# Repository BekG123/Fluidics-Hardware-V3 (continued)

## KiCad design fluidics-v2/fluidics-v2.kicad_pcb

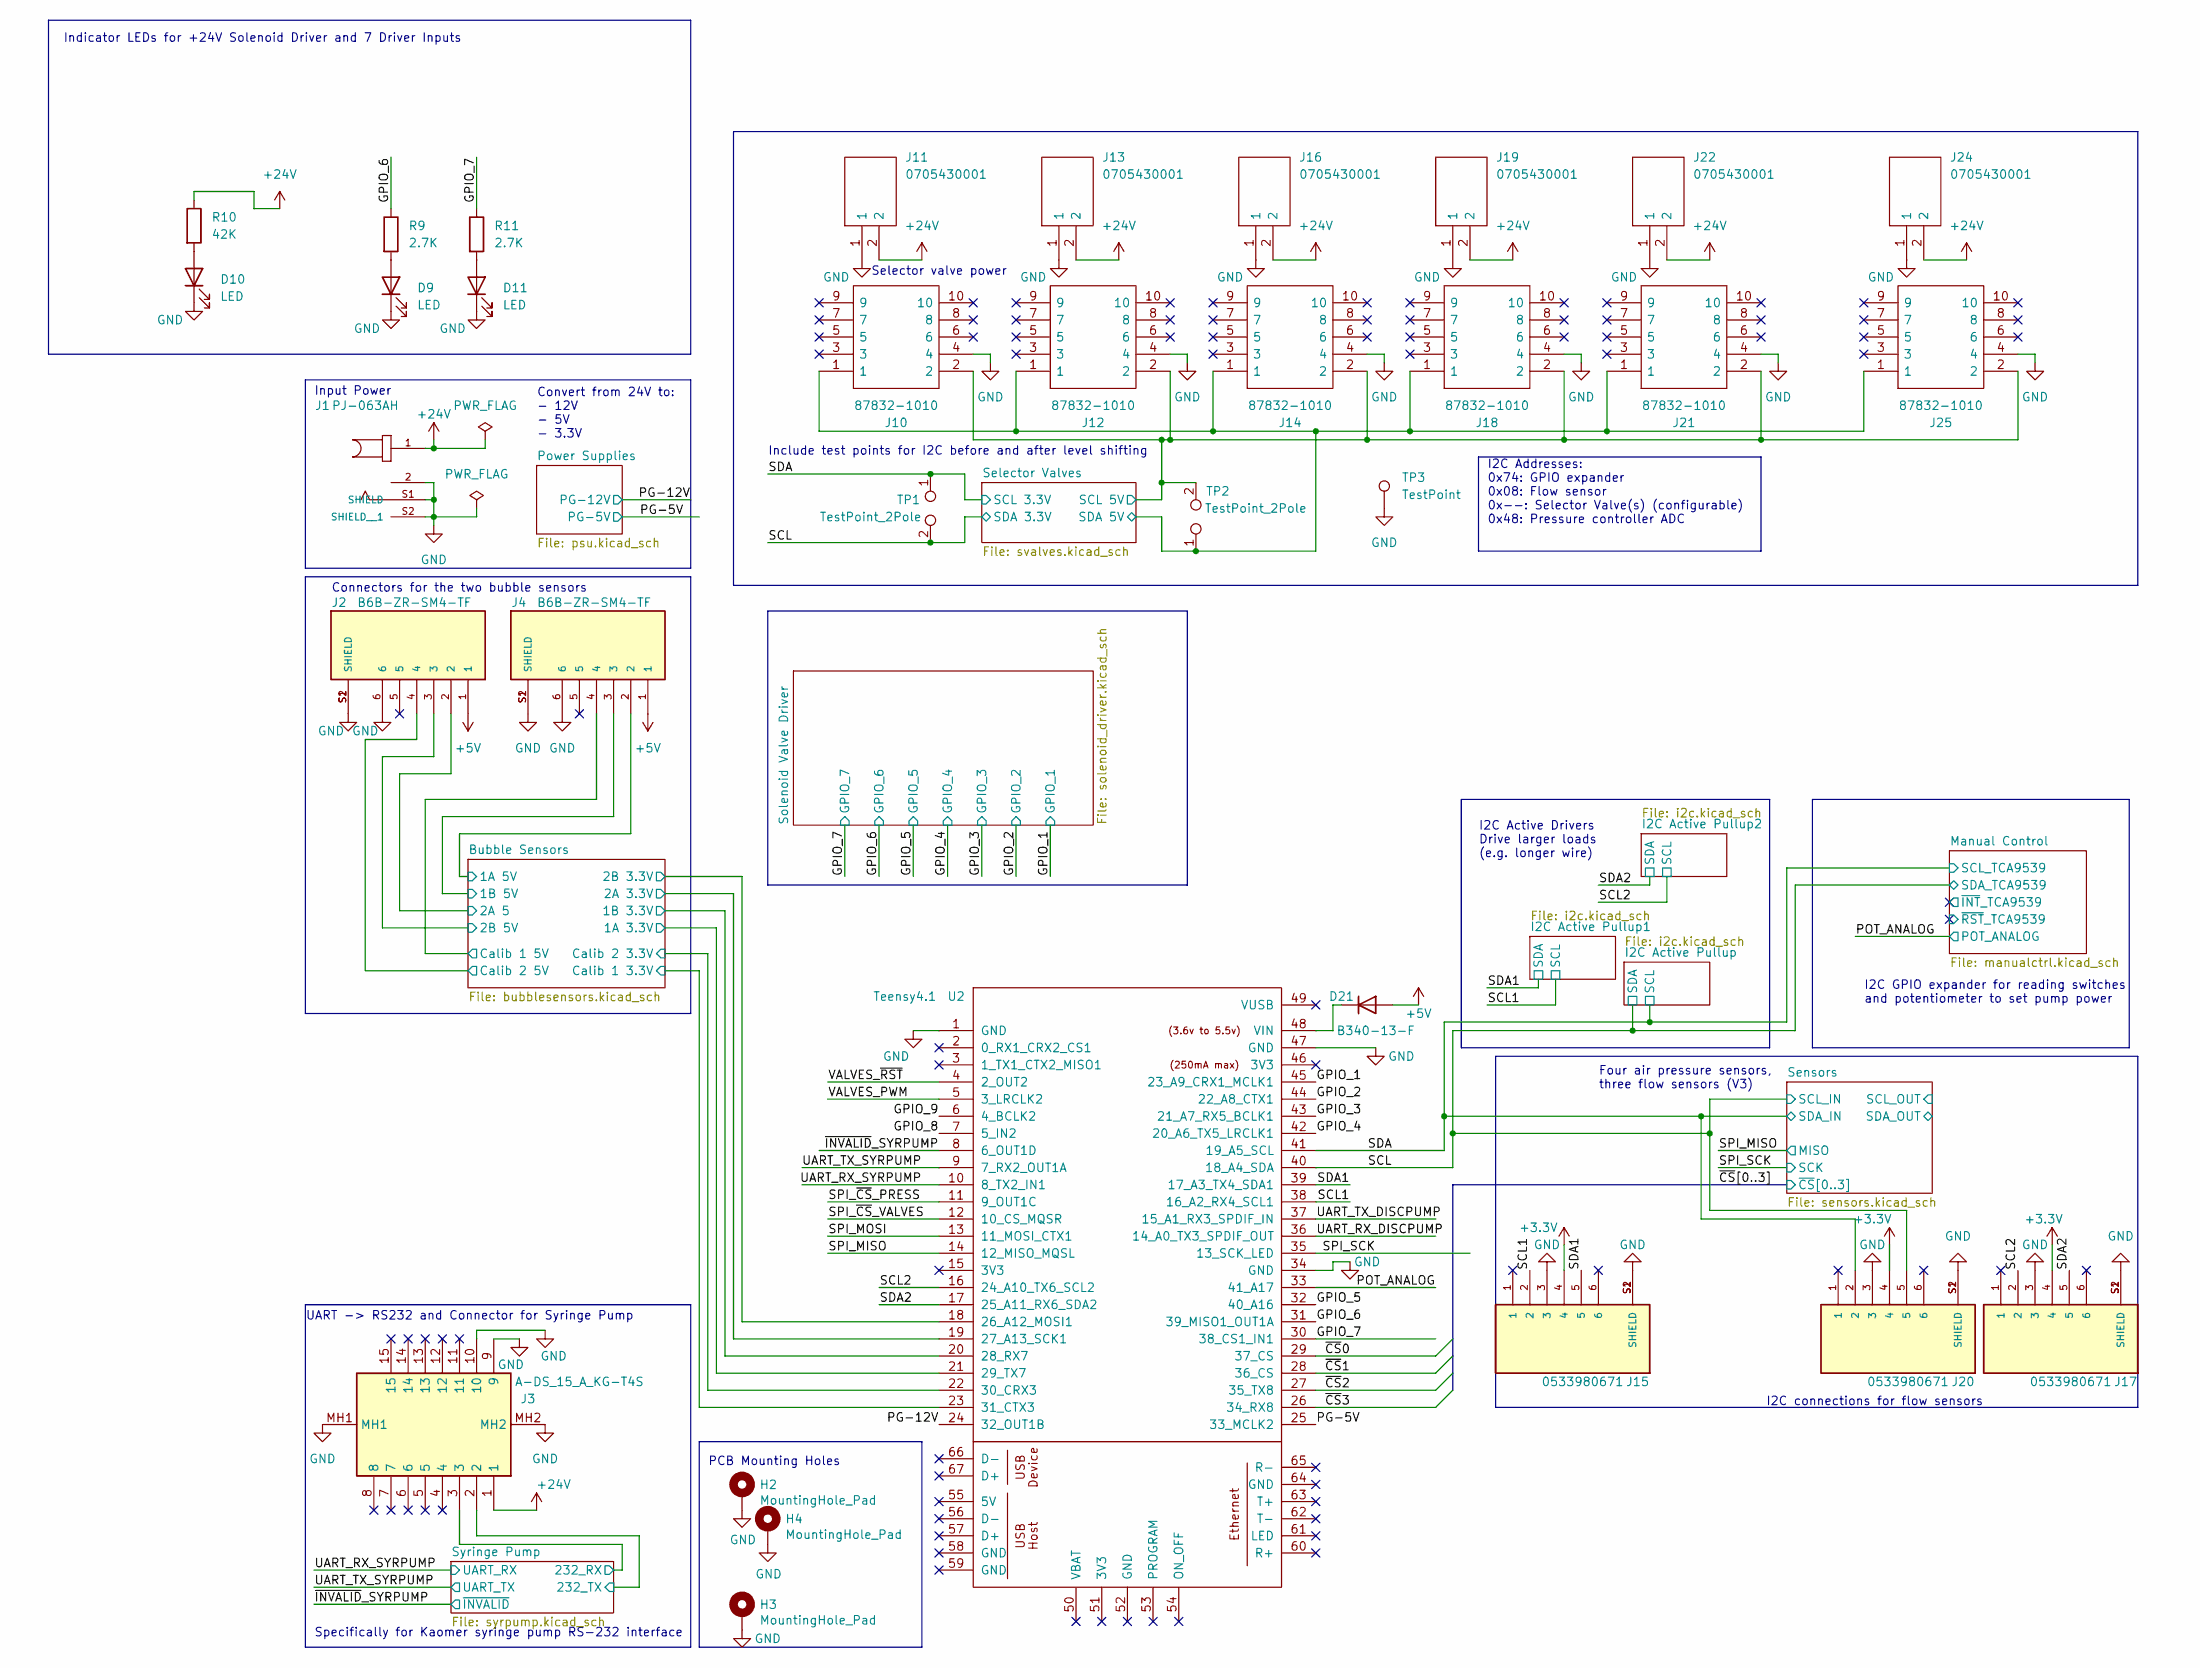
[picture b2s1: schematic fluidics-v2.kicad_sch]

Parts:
D9, D10, D11: LED; LED_0402_1005Metric
D21: B340-13-F; D_SMC
H2, H3, H4: MountingHole_Pad; MountingHole_2.2mm_M2_Pad_Via
J1: PJ-063AH; CUI_PJ-063AH; PARTREV 1.02; LCSC C2928097
J2, J4: B6B-ZR-SM4-TF; CONN_B6B-ZR-SM4-TF_JST
J3: A-DS_15_A_KG-T4S; ADS15AKGT4S; Manufacturer_Part_Number A-DS 15 A/KG-T4S; LCSC C3100941
J10, J12, J14, J18, J21, J25: 87832-1010; 878321010; Manufacturer_Part_Number 87832-1010; Mouser Part Number 538-87832-1010
J11, J13, J16, J19, J22, J24: 0705430001; SHDR2W64P0X254_1X2_737X660X1181P; Manufacturer_Part_Number 0705430001; Mouser Part Number N/A
J15, J17, J20: 0533980671; MOLEX_0533980671; PARTREV A
R9, R11: 2.7K; R_0402_1005Metric
R10: 42K; R_0603_1608Metric
TP1, TP2: TestPoint_2Pole; TestPoint_2Pads_Pitch2.54mm_Drill0.8mm
TP3: TestPoint; TestPoint_THTPad_1.5x1.5mm_Drill0.7mm
U2: Teensy4.1; Teensy 4.1

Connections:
+3.3V: J15.4, J17.4, J20.4; also elsewhere on the board
+5V: D21.2 (A), J2.1, J4.1; also elsewhere on the board
+24V: J1.1, J3.1, J11.2, J13.2, J16.2, J19.2, J22.2, J24.2, R10.1; also elsewhere on the board
/Bubble Sensors/1A 3.3V: U2.21 (29_TX7); also elsewhere on the board
/Bubble Sensors/1A 5V: J4.2; also elsewhere on the board
/Bubble Sensors/1B 3.3V: U2.20 (28_RX7); also elsewhere on the board
/Bubble Sensors/1B 5V: J4.3; also elsewhere on the board
/Bubble Sensors/2A 3.3V: U2.19 (27_A13_SCK1); also elsewhere on the board
/Bubble Sensors/2A 5: J2.2; also elsewhere on the board
/Bubble Sensors/2B 3.3V: U2.18 (26_A12_MOSI1); also elsewhere on the board
/Bubble Sensors/2B 5V: J2.3; also elsewhere on the board
/Bubble Sensors/Calib 1 3.3V: U2.23 (31_CTX3); also elsewhere on the board
/Bubble Sensors/Calib 1 5V: J4.4; also elsewhere on the board
/Bubble Sensors/Calib 2 3.3V: U2.22 (30_CRX3); also elsewhere on the board
/Bubble Sensors/Calib 2 5V: J2.4; also elsewhere on the board
/GPIO_1: U2.45 (23_A9_CRX1_MCLK1); also elsewhere on the board
/GPIO_2: U2.44 (22_A8_CTX1); also elsewhere on the board
/GPIO_3: U2.43 (21_A7_RX5_BCLK1); also elsewhere on the board
/GPIO_4: U2.42 (20_A6_TX5_LRCLK1); also elsewhere on the board
/GPIO_5: U2.32 (40_A16); also elsewhere on the board
/GPIO_6: R9.1, U2.31 (39_MISO1_OUT1A); also elsewhere on the board
/GPIO_7: R11.1, U2.30 (38_CS1_IN1); also elsewhere on the board
/GPIO_8: U2.7 (5_IN2)
/GPIO_9: U2.6 (4_BCLK2)
/PG-5V: U2.25 (33_MCLK2); also elsewhere on the board
/PG-12V: U2.24 (32_OUT1B)
/POT_ANALOG: U2.33 (41_A17)
/SCL: J20.5, TP1.2, U2.40 (18_A4_SDA); also elsewhere on the board
/SCL1: J15.2, U2.38 (16_A2_RX4_SCL1); also elsewhere on the board
/SCL2: J17.2, U2.16 (24_A10_TX6_SCL2); also elsewhere on the board
/SDA: J20.2, TP1.1, U2.41 (19_A5_SCL); also elsewhere on the board
/SDA1: J15.5, U2.39 (17_A3_TX4_SDA1); also elsewhere on the board
/SDA2: J17.5, U2.17 (25_A11_RX6_SDA2); also elsewhere on the board
/SPI_MISO: U2.14 (12_MISO_MQSL)
/SPI_MOSI: U2.13 (11_MOSI_CTX1)
/SPI_SCK: U2.35 (13_SCK_LED)
/SPI_~CS_PRESS: U2.11 (9_OUT1C)
/SPI_~CS_VALVES: U2.12 (10_CS_MQSR)
/Selector Valves/SCL 5V: J10.2, J12.2, J14.2, J18.2, J21.2, J25.2, TP2.2; also elsewhere on the board
/Selector Valves/SDA 5V: J10.1, J12.1, J14.1, J18.1, J21.1, J25.1, TP2.1; also elsewhere on the board
/Syringe Pump/232_RX: J3.3; also elsewhere on the board
/Syringe Pump/232_TX: J3.2; also elsewhere on the board
/UART_RX_DISCPUMP: U2.36 (14_A0_TX3_SPDIF_OUT)
/UART_RX_SYRPUMP: U2.10 (8_TX2_IN1); also elsewhere on the board
/UART_TX_DISCPUMP: U2.37 (15_A1_RX3_SPDIF_IN)
/UART_TX_SYRPUMP: U2.9 (7_RX2_OUT1A); also elsewhere on the board
/VALVES_PWM: U2.5 (3_LRCLK2)
/VALVES_~RST: U2.4 (2_OUT2)
/~CS0: U2.29 (37_CS)
/~CS1: U2.28 (36_CS)
/~CS2: U2.27 (35_TX8)
/~CS3: U2.26 (34_RX8)
/~INVALID_SYRPUMP: U2.8 (6_OUT1D); also elsewhere on the board
GND: D9.1 (K), D10.1 (K), D11.1 (K), H2.1 (1_1), H3.1 (1_1), H4.1 (1_1), J1.2, J1.S1 (SHIELD), J1.S2 (SHIELD__1), J2.6, J2.S1 (SHIELD), J2.S2 (SHIELD), J3.9, J3.10, J3.MH1, J3.MH2, J4.6, J4.S1 (SHIELD), J4.S2 (SHIELD), J10.4, J11.1, J12.4, J13.1, J14.4, J15.3, J15.S1 (SHIELD), J15.S2 (SHIELD), J16.1, J17.3, J17.S1 (SHIELD), J17.S2 (SHIELD), J18.4, J19.1, J20.3, J20.S1 (SHIELD), J20.S2 (SHIELD), J21.4, J22.1, J24.1, J25.4, TP3.1 (1_1), U2.1 (GND), U2.34 (GND), U2.47 (GND); also elsewhere on the board
unnamed: D9.2 (A), R9.2
unnamed: D10.2 (A), R10.2
unnamed: D11.2 (A), R11.2
unnamed: D21.1 (K), U2.48 (VIN)

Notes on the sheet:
I2C connections for flow sensors
Indicator LEDs for +24V Solenoid Driver and 7 Driver Inputs
Four air pressure sensors, three flow sensors (V3)
Include test points for I2C before and after level shifting
UART -> RS232 and Connector for Syringe Pump
PCB Mounting Holes
Convert from 24V to: - 12V - 5V - 3.3V
Input Power
I2C GPIO expander for reading switches and potentiometer to set pump power
Selector valve power
I2C Addresses: 0x74: GPIO expander 0x08: Flow sensor 0x--: Selector Valve(s) (configurable) 0x48: Pressure controller ADC
Specifically for Kaomer syringe pump RS-232 interface
Connectors for the two bubble sensors
I2C Active Drivers Drive larger loads (e.g. longer wire)

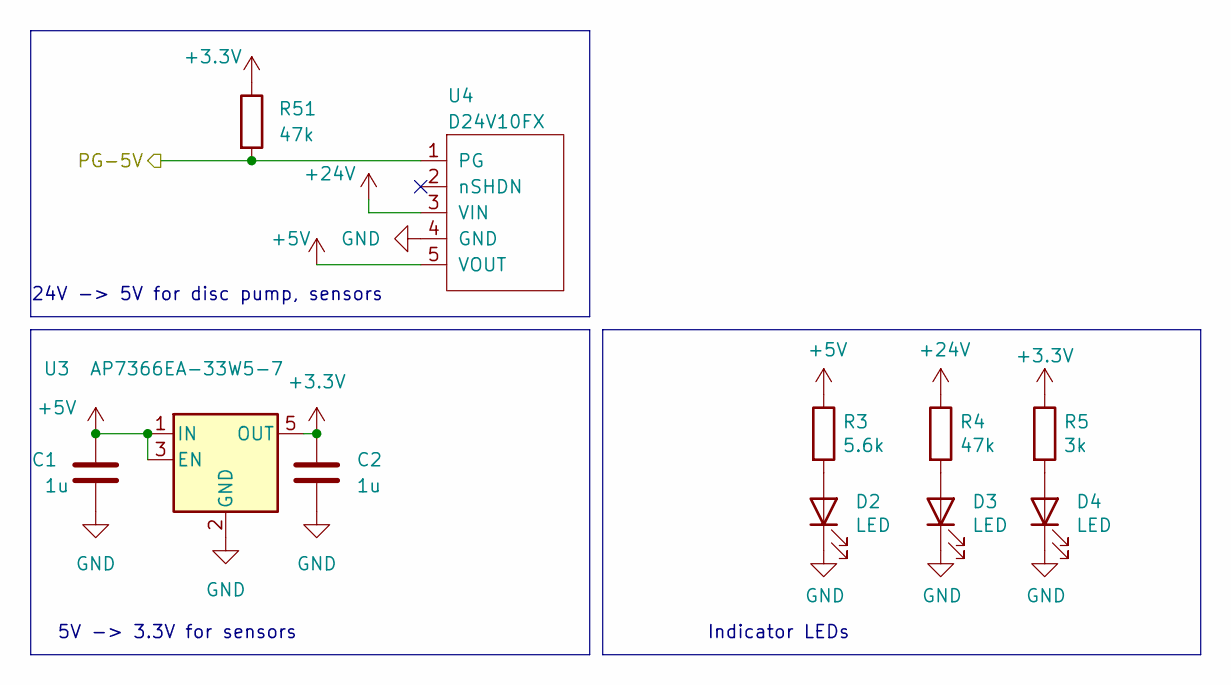
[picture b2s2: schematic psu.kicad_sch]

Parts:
C1, C2: 1u; C_0603_1608Metric
D2, D3: LED; LED_0805_2012Metric; Manufacturer_Part_Number LTST-C170TGKT; LCSC Part # C73546
D4: LED; LED_0805_2012Metric; Manufacturer_Part_Number EAST2012WA1; LCSC Part # C83960
R3: 5.6k; R_0805_2012Metric; Manufacturer_Part_Number RT0603DRD07680RL
R4: 47k; R_0402_1005Metric; Manufacturer_Part_Number RC0603FR-074K7L
R5: 3k; R_0402_1005Metric; Manufacturer_Part_Number RC0603FR-07270RL
R51: 47k; R_0603_1608Metric_Pad0.98x0.95mm_HandSolder
U3: AP7366EA-33W5-7; SOT-23-5
U4: D24V10FX

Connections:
+3.3V: C2.1, R5.1, R51.1, U3.5 (OUT); also elsewhere on the board
+5V: C1.1, R3.1, U3.1 (IN), U3.3 (EN), U4.5 (VOUT); also elsewhere on the board
+24V: R4.1, U4.3 (VIN); also elsewhere on the board
/PG-5V: R51.2, U4.1 (PG); also elsewhere on the board
GND: C1.2, C2.2, D2.1 (K), D3.1 (K), D4.1 (K), U3.2 (GND), U4.4 (GND); also elsewhere on the board
unnamed: D2.2 (A), R3.2
unnamed: D3.2 (A), R4.2
unnamed: D4.2 (A), R5.2

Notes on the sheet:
5V -> 3.3V for sensors
24V -> 5V for disc pump, sensors
Indicator LEDs

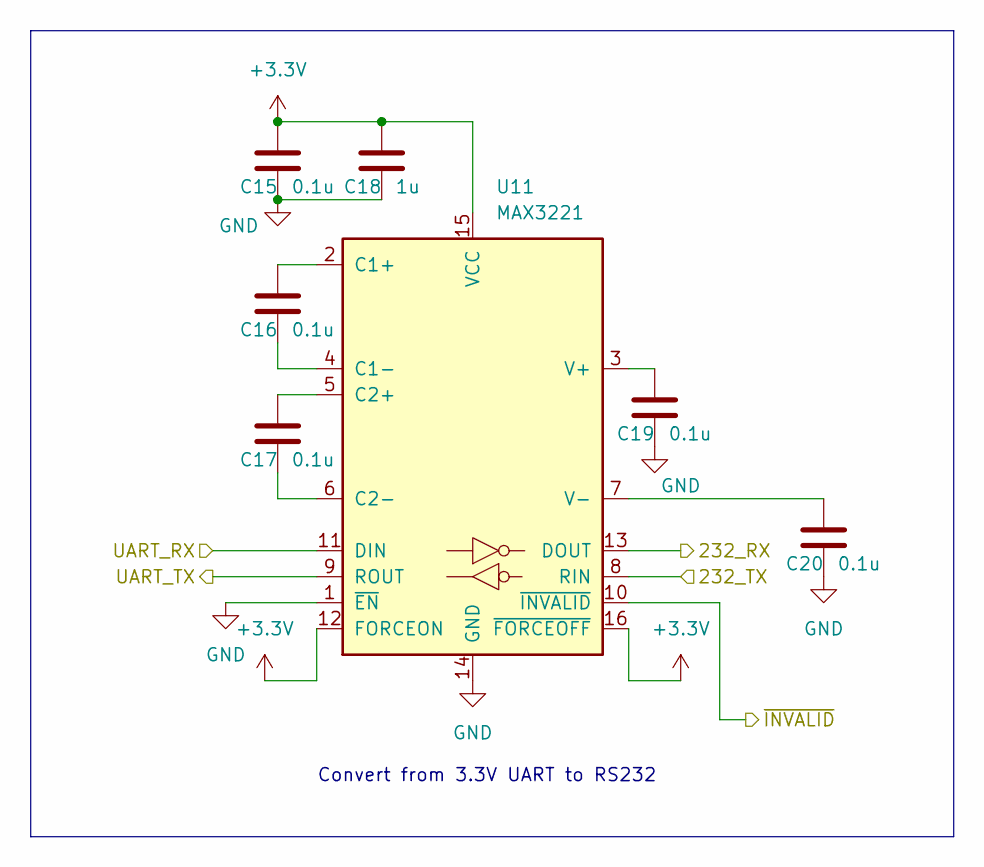
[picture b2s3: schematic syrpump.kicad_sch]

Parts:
C15, C16, C17, C19, C20: 0.1u; C_0603_1608Metric
C18: 1u; C_0805_2012Metric
U11: MAX3221; SOP65P640X120-16N

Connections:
+3.3V: C15.1, C18.1, U11.12 (FORCEON), U11.15 (VCC), U11.16 (~FORCEOFF); also elsewhere on the board
/Syringe Pump/232_RX: U11.13 (DOUT); also elsewhere on the board
/Syringe Pump/232_TX: U11.8 (RIN); also elsewhere on the board
/UART_RX_SYRPUMP: U11.11 (DIN); also elsewhere on the board
/UART_TX_SYRPUMP: U11.9 (ROUT); also elsewhere on the board
/~INVALID_SYRPUMP: U11.10 (~INVALID); also elsewhere on the board
GND: C15.2, C18.2, C19.2, C20.2, U11.1 (~EN), U11.14 (GND); also elsewhere on the board
unnamed: C16.1, U11.2 (C1+)
unnamed: C16.2, U11.4 (C1-)
unnamed: C17.1, U11.5 (C2+)
unnamed: C17.2, U11.6 (C2-)
unnamed: C19.1, U11.3 (V+)
unnamed: C20.1, U11.7 (V-)

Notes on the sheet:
Convert from 3.3V UART to RS232

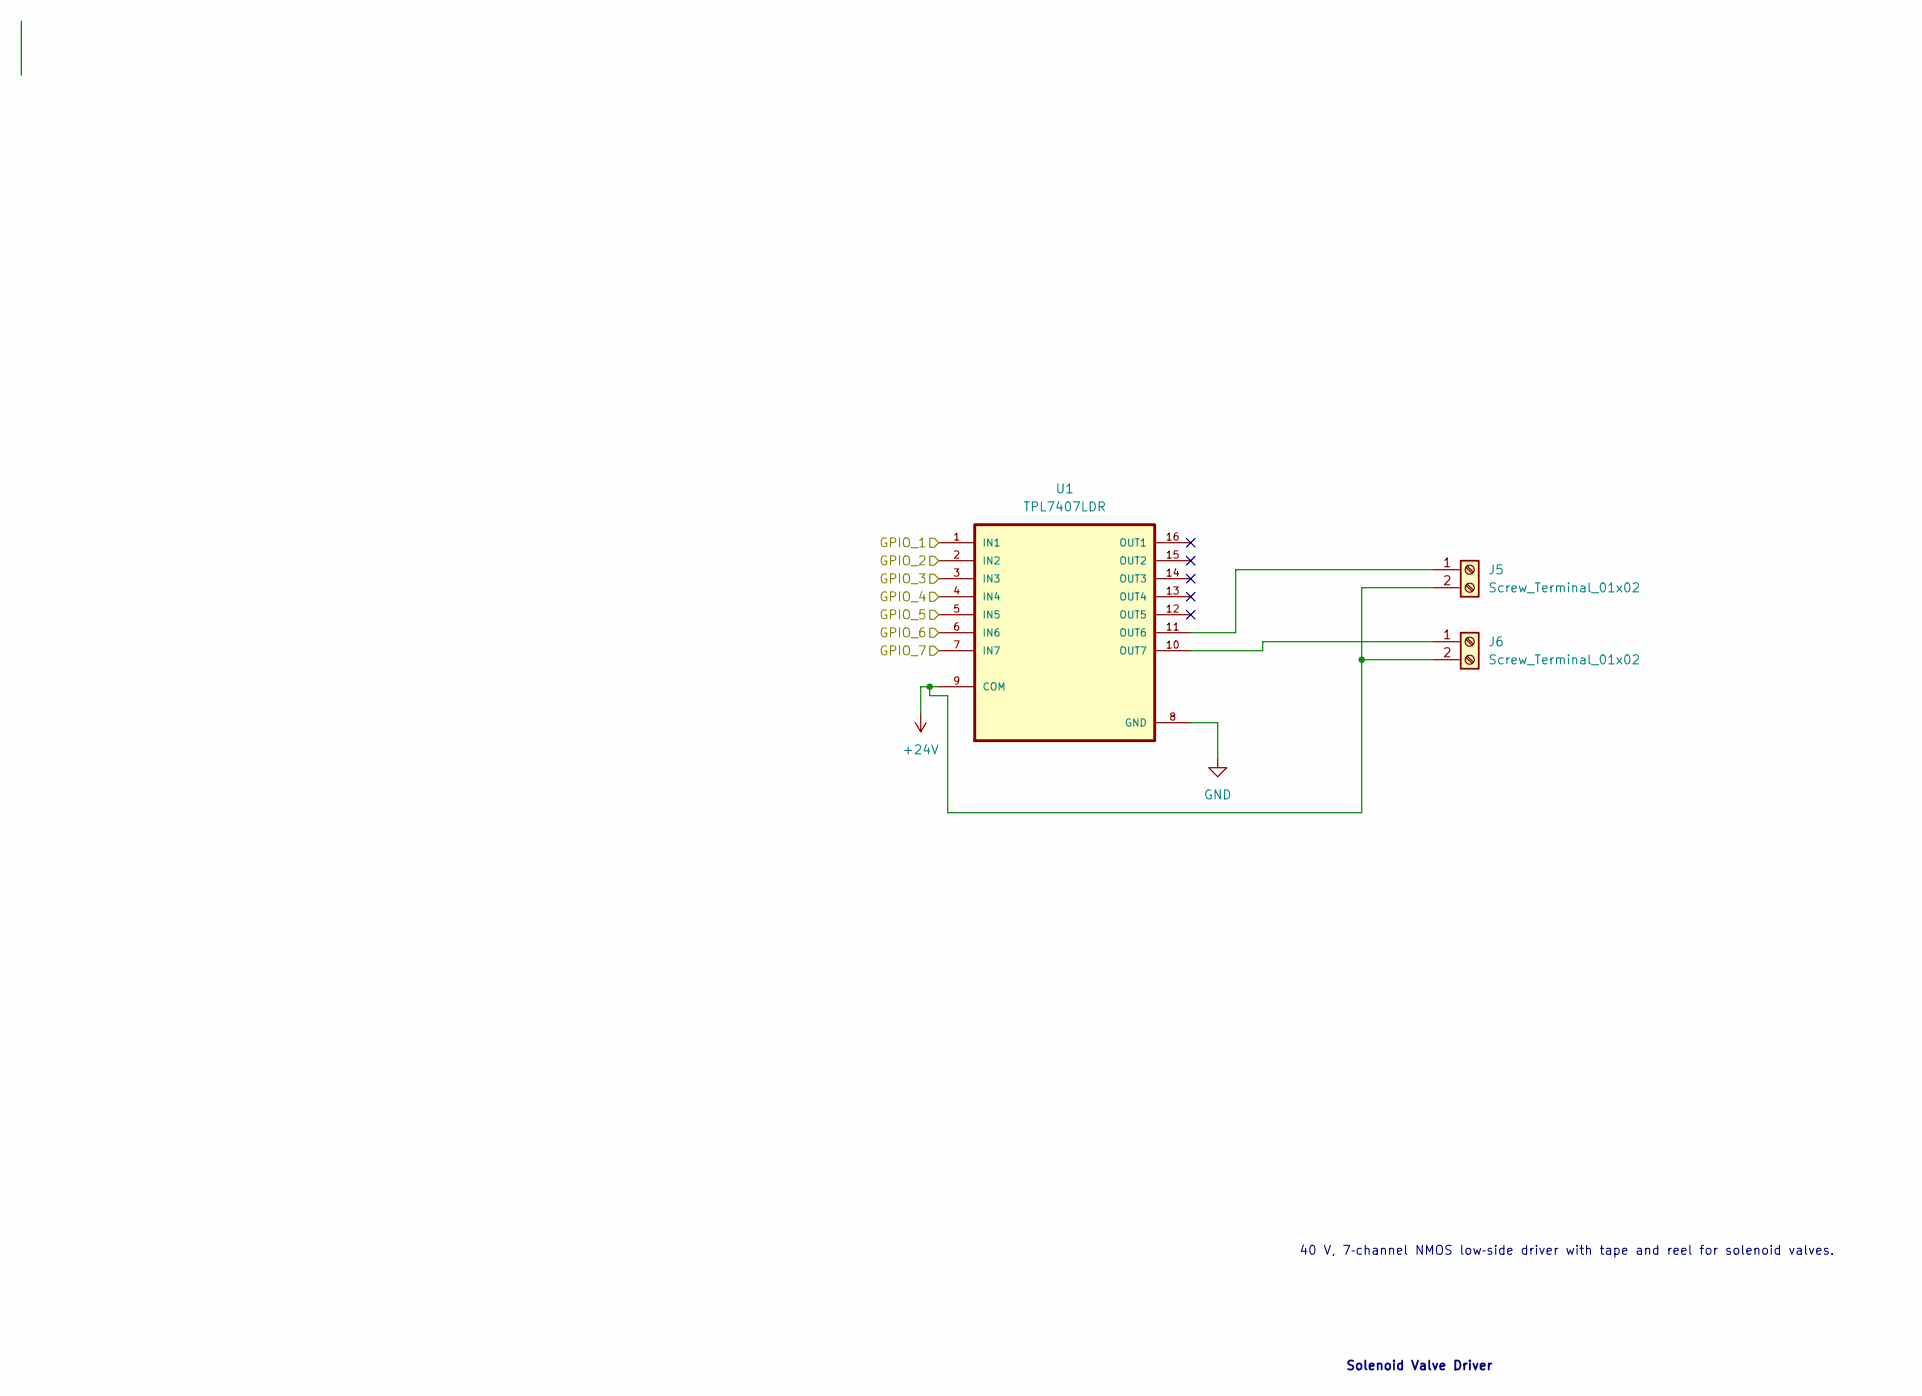
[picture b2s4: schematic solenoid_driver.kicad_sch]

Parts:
J5, J6: Screw_Terminal_01x02; TerminalBlock_Phoenix_MKDS-1,5-2-5.08_1x02_P5.08mm_Horizont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
U1: TPL7407LDR; SOIC127P600X175-16N

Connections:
+24V: J5.2, J6.2, U1.9 (COM); also elsewhere on the board
/GPIO_1: U1.1 (IN1); also elsewhere on the board
/GPIO_2: U1.2 (IN2); also elsewhere on the board
/GPIO_3: U1.3 (IN3); also elsewhere on the board
/GPIO_4: U1.4 (IN4); also elsewhere on the board
/GPIO_5: U1.5 (IN5); also elsewhere on the board
/GPIO_6: U1.6 (IN6); also elsewhere on the board
/GPIO_7: U1.7 (IN7); also elsewhere on the board
GND: U1.8 (GND); also elsewhere on the board
unnamed: J5.1, U1.11 (OUT6)
unnamed: J6.1, U1.10 (OUT7)

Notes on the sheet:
Solenoid Valve Driver
40 V, 7‑channel NMOS low‑side driver with tape and reel for solenoid valves.

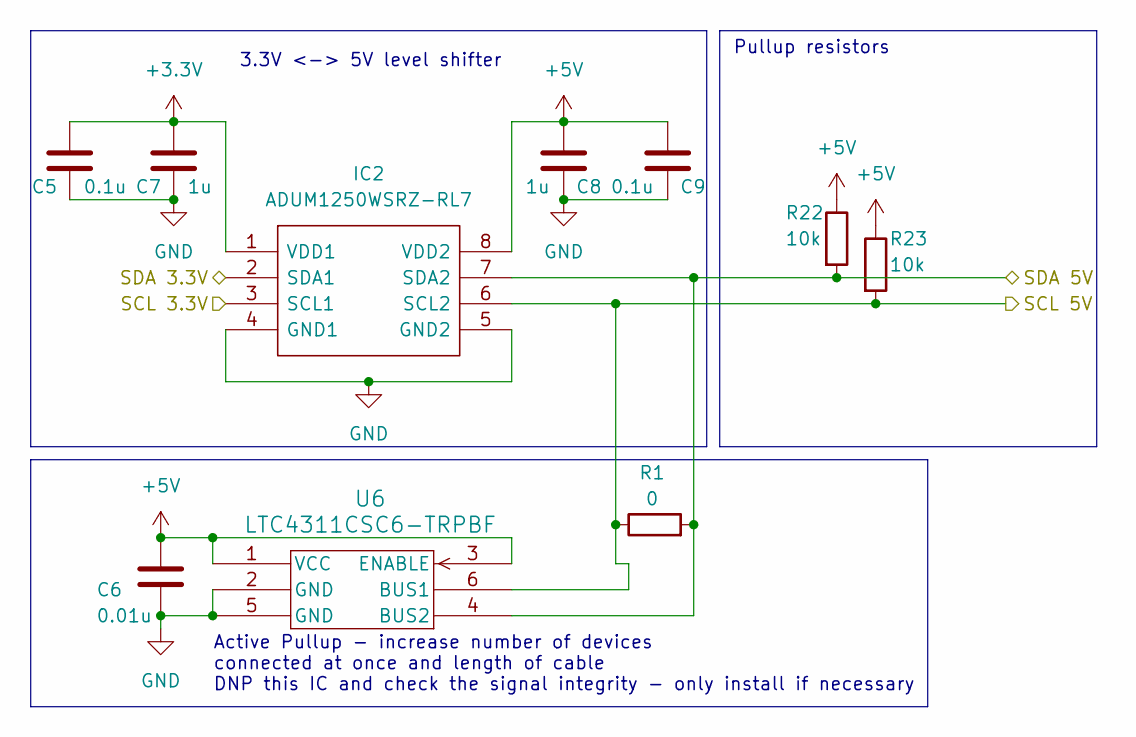
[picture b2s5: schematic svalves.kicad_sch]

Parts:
C5, C9: 0.1u; C_0603_1608Metric
C6: 0.01u; C_0603_1608Metric
C7, C8: 1u; C_0805_2012Metric
IC2: ADUM1250WSRZ-RL7; SOIC127P600X175-8N; Manufacturer_Part_Number ADUM1250WSRZ-RL7; Mouser Part Number 584-ADUM1250WSRZ-RL7
R1: 0; R_0402_1005Metric
R22, R23: 10k; R_0402_1005Metric
U6: LTC4311CSC6-TRPBF; SOT-6_SC_LIT-L

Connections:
+3.3V: C5.1, C7.1, IC2.1 (VDD1); also elsewhere on the board
+5V: C6.1, C8.1, C9.1, IC2.8 (VDD2), R22.1, R23.1, U6.1 (VCC), U6.3 (ENABLE); also elsewhere on the board
/SCL: IC2.2 (SDA1); also elsewhere on the board
/SDA: IC2.3 (SCL1); also elsewhere on the board
/Selector Valves/SCL 5V: IC2.6 (SCL2), R1.1, R23.2, U6.6 (BUS1); also elsewhere on the board
/Selector Valves/SDA 5V: IC2.7 (SDA2), R1.2, R22.2, U6.4 (BUS2); also elsewhere on the board
GND: C5.2, C6.2, C7.2, C8.2, C9.2, IC2.4 (GND1), IC2.5 (GND2), U6.2 (GND), U6.5 (GND); also elsewhere on the board

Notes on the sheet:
Pullup resistors
Active Pullup - increase number of devices connected at once and length of cable DNP this IC and check the signal integrity - only install if necessary
3.3V <-> 5V level shifter

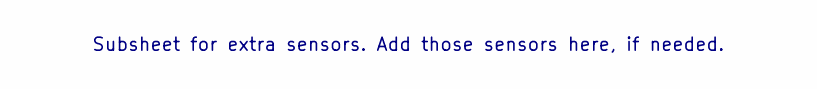
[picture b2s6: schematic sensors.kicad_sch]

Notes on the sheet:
Subsheet for extra sensors. Add those sensors here, if needed.

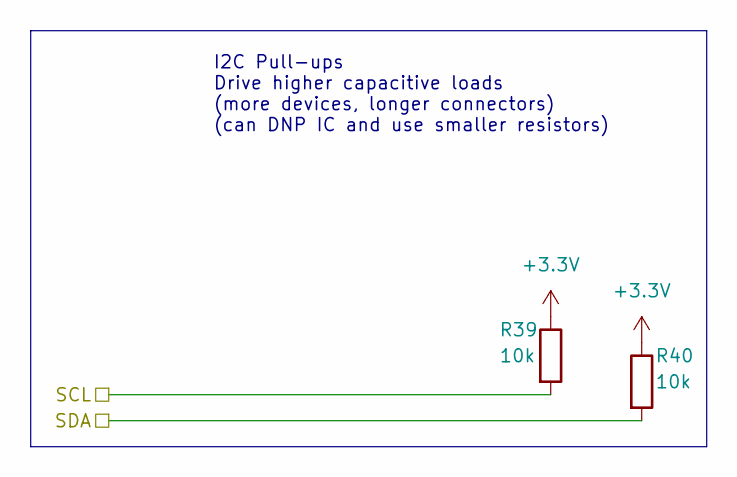
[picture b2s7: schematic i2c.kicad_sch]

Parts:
R39, R40: 10k; R_0402_1005Metric

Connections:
+3.3V: R39.1, R40.1; also elsewhere on the board
/SCL1: R39.2; also elsewhere on the board
/SDA1: R40.2; also elsewhere on the board

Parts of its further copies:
R41, R42, R43, R44: 10k; R_0402_1005Metric

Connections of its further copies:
+3.3V: R41.1, R42.1, R43.1, R44.1; also elsewhere on the board
/SCL: R44.2; also elsewhere on the board
/SCL2: R41.2; also elsewhere on the board
/SDA: R43.2; also elsewhere on the board
/SDA2: R42.2; also elsewhere on the board

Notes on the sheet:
I2C Pull-ups Drive higher capacitive loads (more devices, longer connectors) (can DNP IC and use smaller resistors)

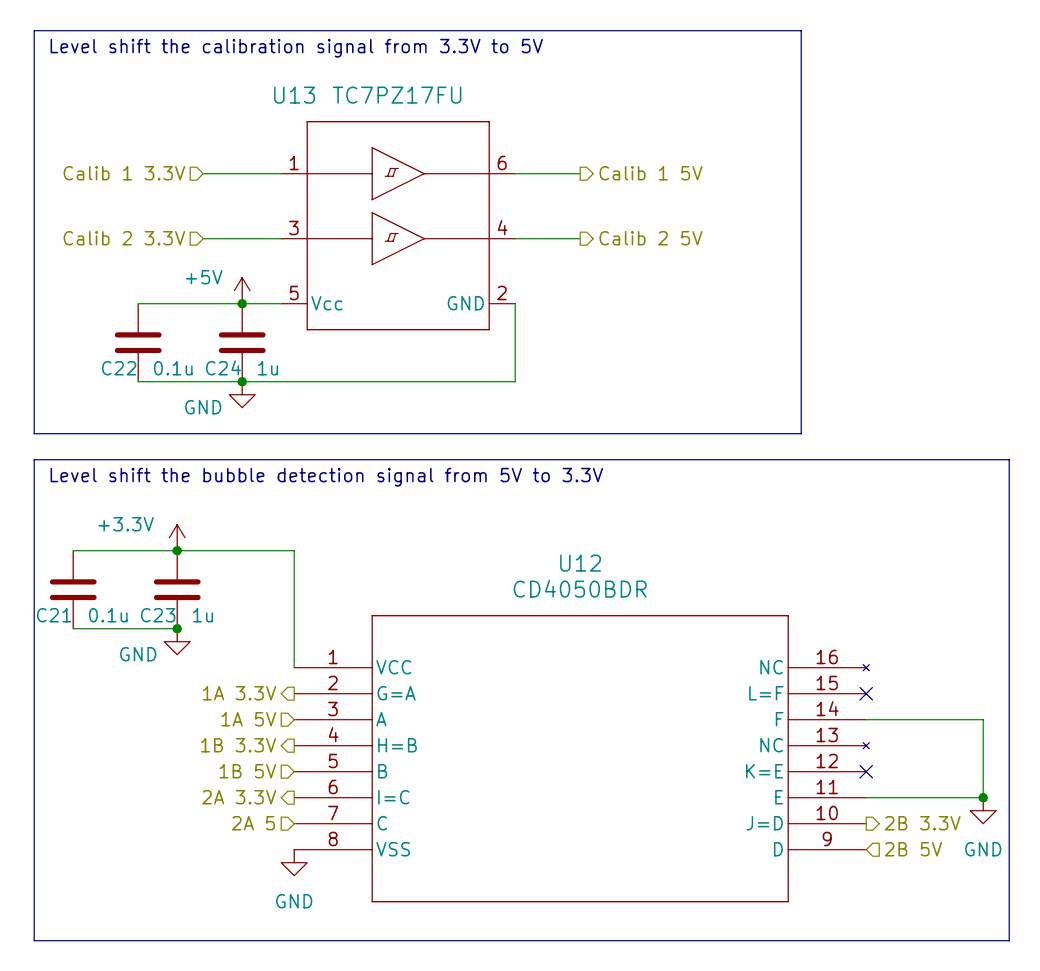
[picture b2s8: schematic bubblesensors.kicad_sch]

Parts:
C21, C22: 0.1u; C_0603_1608Metric
C23, C24: 1u; C_0805_2012Metric
U12: CD4050BDR; D16
U13: TC7PZ17FU; SOT-363 US6_TOS

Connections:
+3.3V: C21.1, C23.1, U12.1 (VCC); also elsewhere on the board
+5V: C22.1, C24.1, U13.5 (Vcc); also elsewhere on the board
/Bubble Sensors/1A 3.3V: U12.2 (G=A); also elsewhere on the board
/Bubble Sensors/1A 5V: U12.3 (A); also elsewhere on the board
/Bubble Sensors/1B 3.3V: U12.4 (H=B); also elsewhere on the board
/Bubble Sensors/1B 5V: U12.5 (B); also elsewhere on the board
/Bubble Sensors/2A 3.3V: U12.6 (I=C); also elsewhere on the board
/Bubble Sensors/2A 5: U12.7 (C); also elsewhere on the board
/Bubble Sensors/2B 3.3V: U12.10 (J=D); also elsewhere on the board
/Bubble Sensors/2B 5V: U12.9 (D); also elsewhere on the board
/Bubble Sensors/Calib 1 3.3V: U13.1; also elsewhere on the board
/Bubble Sensors/Calib 1 5V: U13.6; also elsewhere on the board
/Bubble Sensors/Calib 2 3.3V: U13.3; also elsewhere on the board
/Bubble Sensors/Calib 2 5V: U13.4; also elsewhere on the board
GND: C21.2, C22.2, C23.2, C24.2, U12.8 (VSS), U12.11 (E), U12.14 (F), U13.2 (GND); also elsewhere on the board

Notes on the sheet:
Level shift the bubble detection signal from 5V to 3.3V
Level shift the calibration signal from 3.3V to 5V

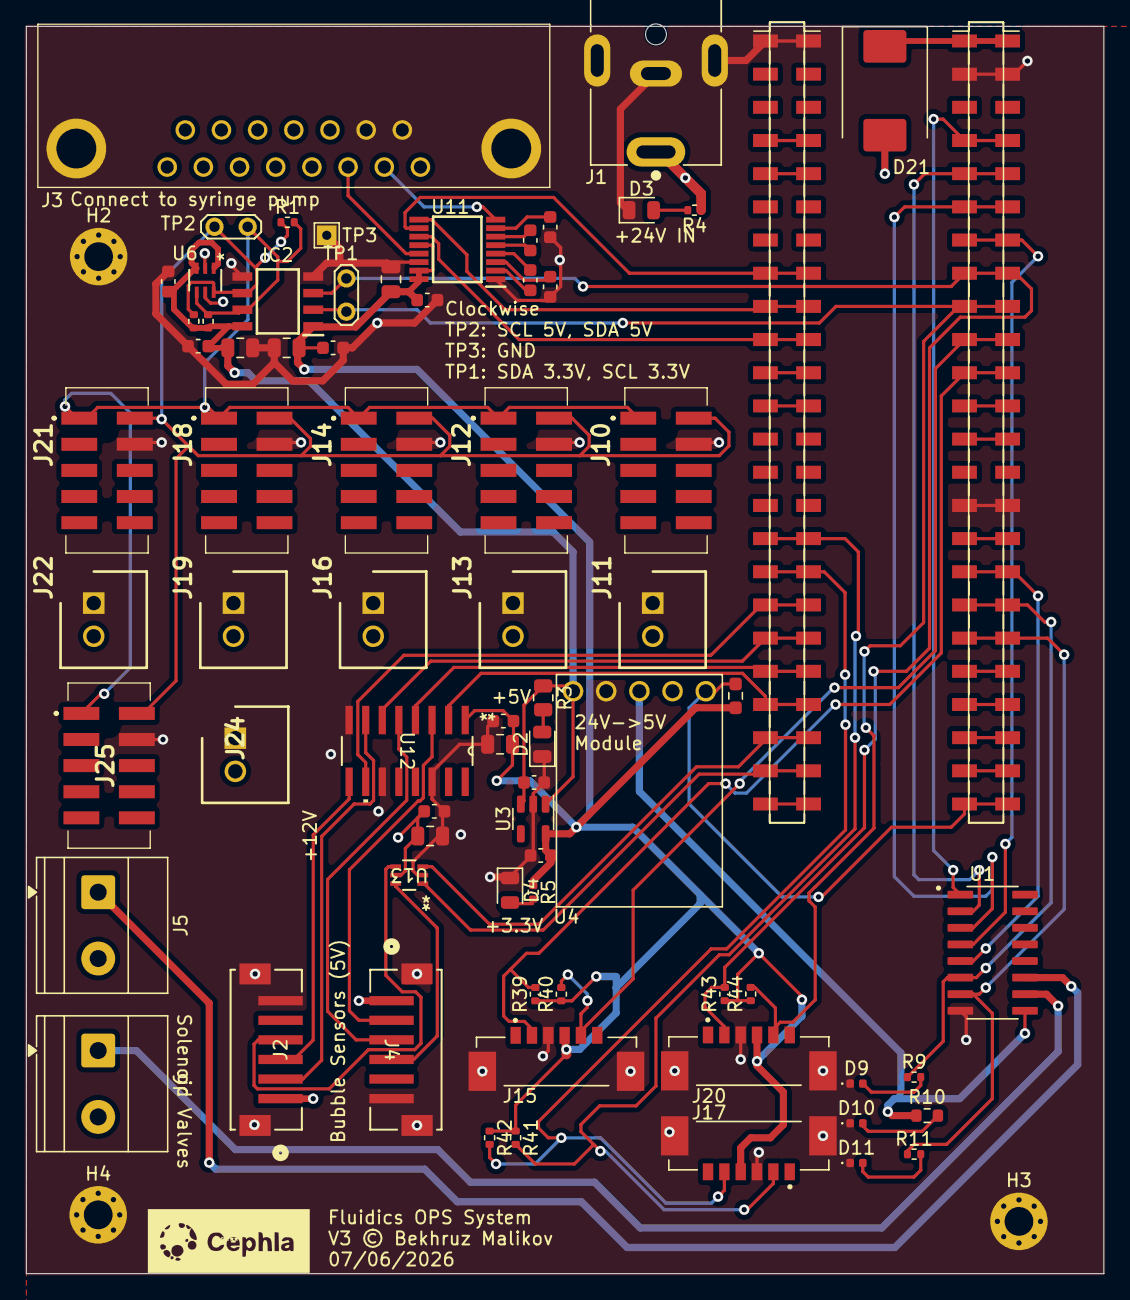
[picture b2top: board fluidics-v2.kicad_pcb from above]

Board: 4 copper layers, 82.5 x 95.5 mm, 76 parts (0 on the bottom side), 52 nets.

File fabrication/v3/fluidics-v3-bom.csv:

"Designator","Value","Footprint","MPN","Manufacturer","LCSC","Qty","DNP"
"C1,C2","1u","Capacitor_SMD:C_0603_1608Metric","","","","2",""
"C3","100u","Capacitor_Tantalum_SMD:CP_EIA-7343-20_Kemet-V","","","","1",""
"C4","47u","Capacitor_SMD:C_1206_3216Metric","","","","1",""
"C5,C9,C11,C13,C15,C16,C17,C19,C20,C21,C22,C25","0.1u","Capacitor_SMD:C_0603_1608Metric","","","","12",""
"C7,C8,C18,C23,C24","1u","Capacitor_SMD:C_0805_2012Metric","","","","5",""
"C10","100u","Capacitor_SMD:C_1210_3225Metric","","","","1",""
"C12","470u 50V","Capacitor_THT:CP_Radial_D10.0mm_P5.00mm","","","","1",""
"D2,D3","LED","LED_SMD:LED_0805_2012Metric","LTST-C170TGKT","","","2",""
"D4","LED","LED_SMD:LED_0805_2012Metric","EAST2012WA1","","","1",""
"D9,D10,D11,D12","LED","LED_SMD:LED_0402_1005Metric","","","","4",""
"D21","B340-13-F","Diode_SMD:D_SMC","","","","1",""
"IC2","ADUM1250WSRZ-RL7","analog_devices:SOIC127P600X175-8N","ADUM1250WSRZ-RL7","Analog Devices","","1",""
"J1","PJ-063AH","barreljack:CUI_PJ-063AH","PJ-063AH","CUI Devices","C2928097","1",""
"J2,J4","B6B-ZR-SM4-TF","B6B-ZR-SM4-TF:CONN_B6B-ZR-SM4-TF_JST","","JST","","2",""
"J3","A-DS_15_A_KG-T4S","db15:ADS15AKGT4S","A-DS 15 A/KG-T4S","ASSMANN WSW components GmbH","C3100941","1",""
"J5","Screw_Terminal_01x06","TerminalBlock:TerminalBlock_Xinya_XY308-2.54-6P_1x06_P2.54mm_Horizontal","","","","1",""
"J10,J12,J14,J18,J21,J25","87832-0410","molex_connectors:878320410","87832-0410","Molex","","6",""
"J11,J13,J16,J19,J22,J24","0705430001","molex_connectors:SHDR2W64P0X254_1X2_737X660X1181P","0705430001","Molex","C5349069","6",""
"J15,J17,J20","0533980671","molex_connectors:MOLEX_0533980671","","Molex","","3",""
"Q1","F60N80","Package_TO_SOT_THT:TO-220-3_Vertical","","","","1",""
"R2","100k","Resistor_SMD:R_0402_1005Metric","","","","1",""
"R3","5.6k","Resistor_SMD:R_0805_2012Metric","RC0805FR-075K6L","","","1",""
"R4","47k","Resistor_SMD:R_0402_1005Metric","RC0402FR-0747KL","","","1",""
"R5","3k","Resistor_SMD:R_0402_1005Metric","RC0402FR-073KL","","","1",""
"R6","68k","Resistor_SMD:R_0402_1005Metric","","","","1",""
"R9,R11,R12","2.7k","Resistor_SMD:R_0402_1005Metric","","","","3",""
"R10","47k","Resistor_SMD:R_0603_1608Metric","","","","1",""
"R22,R23,R39,R40,R41,R42,R43,R44","2.2k","Resistor_SMD:R_0402_1005Metric","","","","8",""
"U1","TPL7407LDR","TPL7407LDR:SOIC127P600X175-16N","TPL7407LDR","Texas Instruments","","1",""
"U3","AP2112K-3.3TRG1","Package_TO_SOT_SMD:SOT-23-5","","","","1",""
"U4","TSR1-2450E","Converter_DCDC:Converter_DCDC_TRACO_TSR1-xxxxE_THT","","","","1",""
"U11","MAX3221","MAX232:SOP65P640X120-16N","","","","1",""
"U12","CD4050BDR","hexbuf:D16","","","","1",""
"U13","TC7PZ17FU","TC7PZ17FU:SOT-363   US6_TOS","","","","1",""
